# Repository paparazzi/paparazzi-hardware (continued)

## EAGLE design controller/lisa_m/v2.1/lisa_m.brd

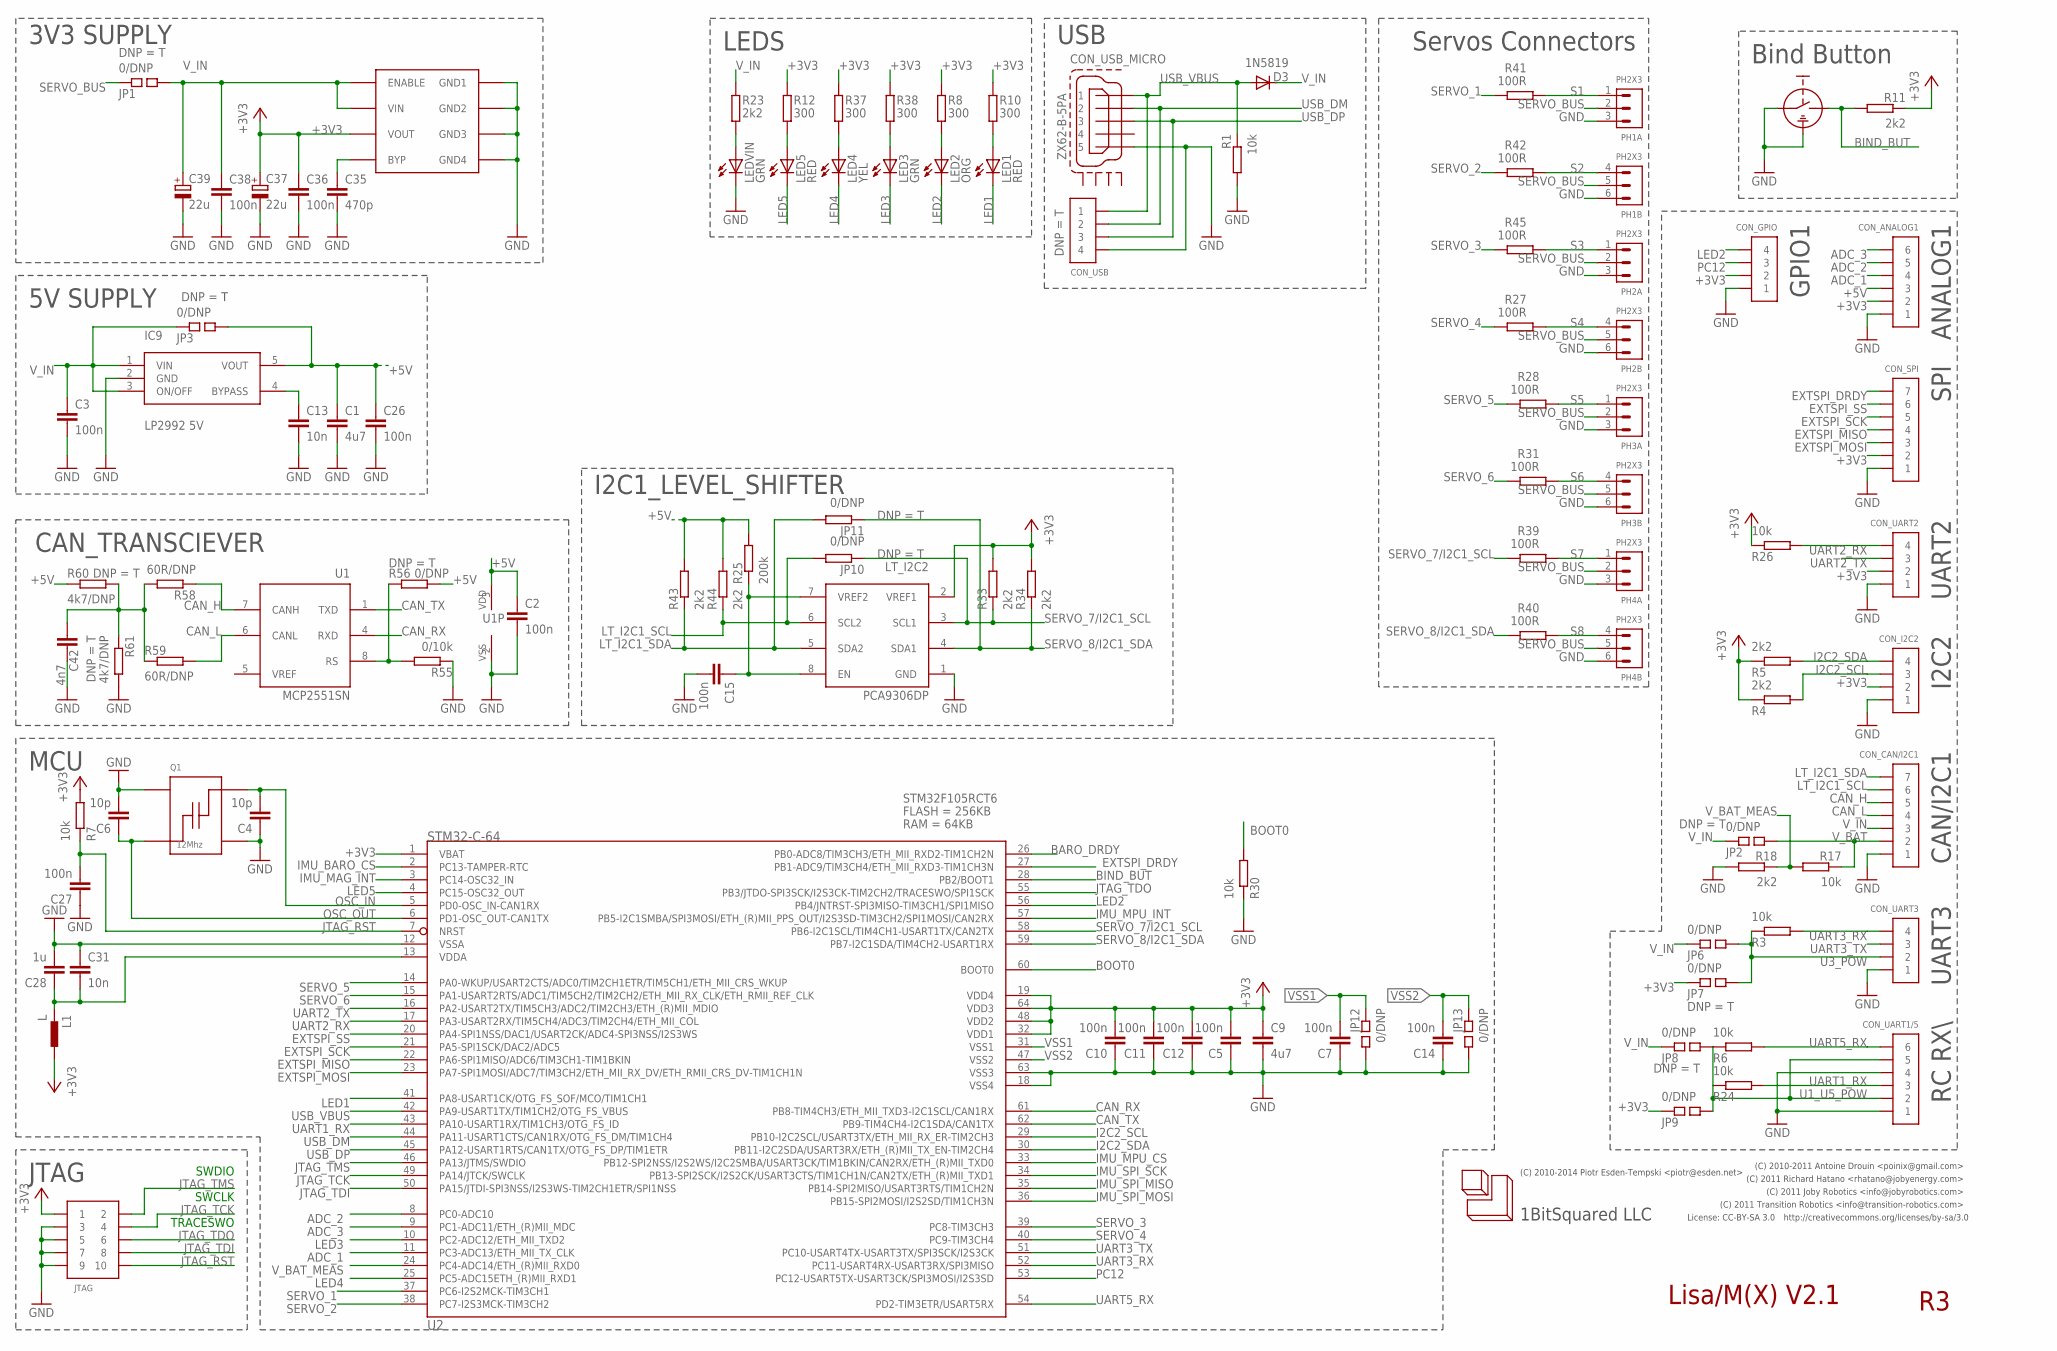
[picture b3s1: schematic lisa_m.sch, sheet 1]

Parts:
C1, C9: 4u7; 0603-CAP; PARTNO cap-cer-0603-4u7
C2, C3, C5, C7, C10, C11, C12, C14, C15, C26, C27, C36, C38: 100n; 0402-CAP; PARTNO cap-cer-0402-100n
C4, C6: 10p; 0402-CAP; PARTNO cap-cer-0402-10p
C13, C31: 10n; 0402-CAP; PARTNO cap-cer-0402-10n
C28: 1u; 0603-CAP; PARTNO cap-cer-0603-1u
C35: 470p; 0402-CAP; PARTNO cap-cer-0402-470p
C37, C39: 22u; 3528/B; PARTNO cap-tan-B-22u-16v
C42: 4n7; 0603-CAP; PARTNO cap-cer-0603-4n7
CON_ANALOG1: CONN_6-1-53398; PB-53398-06; PARTNO conn-picoblade-smd-0.05in-6-vert
CON_CAN/I2C1: CONN_7-1-53398; PB-53398-07; PARTNO conn-picoblade-smd-0.05in-7-vert
CON_GPIO: CONN_4-1-53398; PB-53398-04; PARTNO conn-picoblade-smd-0.05in-4-vert
CON_I2C2: CONN_4-1-53398; PB-53398-04; PARTNO conn-picoblade-smd-0.05in-4-vert
CON_SPI: CONN_7-1-53398; PB-53398-07; PARTNO conn-picoblade-smd-0.05in-7-vert
CON_UART1/5: CONN_6-1PB-53398-06_SMALL; PB-53398-06; PARTNO conn-picoblade-smd-0.05in-6-vert
CON_UART2, CON_UART3: CONN_4-1-53398; PB-53398-04; PARTNO conn-picoblade-smd-0.05in-4-vert
CON_USB: CONN_4-1-53047; PB-53047-04; PARTNO conn-picoblade-th-0.05in-4-vert
CON_USB_MICRO: ZX62-B-5PA; PARTNO conn-smd-usb-micro-b
D3: 1N5819; 0603-DIO; PARTNO diode-schottky-0603
IC9: LP2992 5V; SOT23-5; PARTNO vreg-sot-23-5-5v
JP1, JP2, JP3, JP6, JP7, JP8, JP9, JP12, JP13: 0/DNP; 0402-SQJMP; PARTNO res-0402-0
JP10, JP11: 0/DNP; 0603-RES; PARTNO res-0603-0
JTAG: PIN_HDR_EDG_1.27MM_5-2; FTSH-105-DV; PARTNO conn-smd-0.05in-5-2
L1: L; 0402-IND; PARTNO ferrite-0402-600
LED1: RED; 0402-LED; PARTNO led-0402-red
LED2: ORG; 0402-LED; PARTNO led-0402-org
LED3: GRN; 0402-LED; PARTNO led-0402-grn
LED4: YEL; 0402-LED; PARTNO led-0402-yel
LED5: RED; 0402-LED; PARTNO led-0402-grn
LEDVIN: GRN; 0402-LED; PARTNO led-0402-grn
LT_I2C2: PCA9306DP; TSSOP_B3; PARTNO ic-tssop8-level-trans
PH1, PH2, PH3, PH4: PH2X3; PH010-2-3
Q1: 12Mhz; ABM8; PARTNO xtal-abm8-12mhz
R1, R3, R6, R7, R17, R24, R26, R30: 10k; 0402-RES; PARTNO res-0402-10k
R4, R5, R11, R18, R23, R33, R34, R43, R44: 2k2; 0402-RES; PARTNO res-0402-2k2
R8, R10, R12, R37, R38: 300; 0402-RES; PARTNO res-0402-300
R25: 200k; 0402-RES; PARTNO res-0402-200k
R27, R28, R31, R39, R40, R41, R42, R45: 100R; 0402-RES; PARTNO res-0402-100
R55: 0/10k; 0402-RES; PARTNO res-0402-10k
R56: 0/DNP; 0402-RES; PARTNO res-0402-0
R58, R59: 60R/DNP; 0402-RES; PARTNO res-0402-60.4
R60, R61: 4k7/DNP; 0402-RES; PARTNO res-0402-4k7
SW1: MICROTACT_GND; PARTNO sw-tact-top-gnd-3.0-2.5
U1: MCP2551SN; SO-08; PARTNO ic-so8-can
U2: STM32-C-64; LQFP64; PARTNO ic-mcu-stm32f415rgt6
VREG1: MIC5209; SOIC8; PARTNO vreg-so8-3v3

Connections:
+3V3: C5.P$2 (2), C9.P$1 (1), C10.P$2 (2), C11.P$2 (2), C12.P$2 (2), C36.P$1 (1), C37.+, CON_ANALOG1.2, CON_GPIO.2, CON_I2C2.2, CON_SPI.2, CON_UART2.2, JP7.P$1 (1), JP9.P$1 (1), JTAG.1, L1.P$1 (1), LT_I2C2.2 (VREF1), R4.P$1 (1), R5.P$1 (1), R7.P$2 (2), R8.P$2 (2), R10.P$2 (2), R11.P$1 (1), R12.P$2 (2), R26.P$1 (1), R33.P$2 (2), R34.P$2 (2), R37.P$2 (2), R38.P$2 (2), U2.1 (VBAT), U2.19 (VDD4), U2.32 (VDD1), U2.48 (VDD2), U2.64 (VDD3), VREG1.3 (VOUT); also elsewhere on the board
+5V: C1.P$1 (1), C2.P$1 (1), C26.P$1 (1), CON_ANALOG1.3, IC9.5 (VOUT), JP3.P$2 (2), R25.P$2 (2), R43.P$2 (2), R44.P$2 (2), R56.P$2 (2), R60.P$1 (1), U1.3 (VDD)
ADC_1: CON_ANALOG1.4, U2.11 (PC3-ADC13/ETH_MII_TX_CLK)
ADC_2: CON_ANALOG1.5, U2.8 (PC0-ADC10)
ADC_3: CON_ANALOG1.6, U2.9 (PC1-ADC11/ETH_(R)MII_MDC)
BARO_DRDY: U2.26 (PB0-ADC8/TIM3CH3/ETH_MII_RXD2-TIM1CH2N)
BIND_BUT: R11.P$2 (2), SW1.2, U2.28 (PB2/BOOT1)
BOOT0: R30.P$2 (2), U2.60 (BOOT0)
CAN_CENTER: C42.P$2 (2), R58.P$2 (2), R59.P$1 (1), R60.P$2 (2), R61.P$1 (1)
CAN_H: CON_CAN/I2C1.5, R58.P$1 (1), U1.7 (CANH)
CAN_L: CON_CAN/I2C1.4, R59.P$2 (2), U1.6 (CANL)
CAN_RX: U1.4 (RXD), U2.61 (PB8-TIM4CH3/ETH_MII_TXD3-I2C1SCL/CAN1RX)
CAN_TX: U1.1 (TXD), U2.62 (PB9-TIM4CH4-I2C1SDA/CAN1TX)
EXTSPI_DRDY: CON_SPI.7, U2.27 (PB1-ADC9/TIM3CH4/ETH_MII_RXD3-TIM1CH3N)
EXTSPI_MISO: CON_SPI.4, U2.22 (PA6-SPI1MISO/ADC6/TIM3CH1-TIM1BKIN)
EXTSPI_MOSI: CON_SPI.3, U2.23 (PA7-SPI1MOSI/ADC7/TIM3CH2/ETH_MII_RX_DV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)
EXTSPI_SCK: CON_SPI.5, U2.21 (PA5-SPI1SCK/DAC2/ADC5)
EXTSPI_SS: CON_SPI.6, U2.20 (PA4-SPI1NSS/DAC1/USART2CK/ADC4-SPI3NSS/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)
GND: C1.P$2 (2), C2.P$2 (2), C3.P$2 (2), C4.P$1 (1), C5.P$1 (1), C6.P$2 (2), C7.P$1 (1), C9.P$2 (2), C10.P$1 (1), C11.P$1 (1), C12.P$1 (1), C13.P$2 (2), C14.P$1 (1), C15.P$2 (2), C26.P$2 (2), C27.P$1 (1), C28.P$2 (2), C31.P$1 (1), C35.P$2 (2), C36.P$2 (2), C37.-, C38.P$2 (2), C39.-, C42.P$1 (1), CON_ANALOG1.1, CON_CAN/I2C1.1, CON_GPIO.1, CON_I2C2.1, CON_SPI.1, CON_UART1/5.1, CON_UART1/5.4, CON_UART2.1, CON_UART3.1, CON_USB.4, CON_USB_MICRO.PIN_5 (5), IC9.2 (GND), JP12.P$2 (2), JP13.P$2 (2), JTAG.3, JTAG.5, JTAG.7, JTAG.9, LEDVIN.C, LT_I2C2.1 (GND), PH1.3, PH1.6 (3), PH2.3, PH2.6 (3), PH3.3, PH3.6 (3), PH4.3, PH4.6 (3), Q1.P$2, Q1.P$4, R1.P$2 (2), R18.P$2 (2), R30.P$1 (1), R55.P$1 (1), R61.P$2 (2), SW1.1, SW1.G (GND), U1.2 (VSS), U2.12 (VSSA), U2.18 (VSS4), U2.63 (VSS3), VREG1.5 (GND4), VREG1.6 (GND3), VREG1.7 (GND2), VREG1.8 (GND1); also elsewhere on the board
I2C2_SCL: CON_I2C2.3, R4.P$2 (2), U2.29 (PB10-I2C2SCL/USART3TX/ETH_MII_RX_ER-TIM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)
I2C2_SDA: CON_I2C2.4, R5.P$2 (2), U2.30 (PB11-I2C2SDA/USART3RX/ETH_(R)MII_TX_EN-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)
IMU_BARO_CS: U2.2 (PC13-TAMPER-RTC); also elsewhere on the board
IMU_MAG_INT: U2.3 (PC14-OSC32_IN); also elsewhere on the board
IMU_MPU_CS: U2.33 (PB12-SPI2NSS/I2S2WS/I2C2SMBA/USART3CK/T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); also elsewhere on the board
IMU_MPU_INT: U2.57 (PB5-I2C1SMBA/SPI3MOSI/ETH_(R)MII_PPS_OU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); also elsewhere on the board
IMU_SPI_MISO: U2.35 (PB14-SPI2MISO/USART3RTS/TIM1CH2N); also elsewhere on the board
IMU_SPI_MOSI: U2.36 (PB15-SPI2MOSI/I2S2SD/TIM1CH3N); also elsewhere on the board
IMU_SPI_SCK: U2.34 (PB13-SPI2SCK/I2S2CK/USART3CTS/TIM1CH1N/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); also elsewhere on the board
JTAG_RST: C27.P$2 (2), JTAG.10, R7.P$1 (1), U2.7 (NRST)
JTAG_TCK: JTAG.4, U2.49 (PA14/JTCK/SWCLK)
JTAG_TDI: JTAG.8, U2.50 (PA15/JTDI-SPI3NSS/I2S3WS-TIM2CH1ETR/SPI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)
JTAG_TDO: JTAG.6, U2.55 (PB3/JTDO-SPI3SCK/I2S3CK-TIM2CH2/TRACESW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)
JTAG_TMS: JTAG.2, U2.46 (PA13/JTMS/SWDIO)
LED1: LED1.C, U2.41 (PA8-USART1CK/OTG_FS_SOF/MCO/TIM1CH1)
LED2: CON_GPIO.4, LED2.C, U2.56 (PB4/JNTRST-SPI3MISO-TIM3CH1/SPI1MISO)
LED3: LED3.C, U2.10 (PC2-ADC12/ETH_MII_TXD2)
LED4: LED4.C, U2.25 (PC5-ADC15ETH_(R)MII_RXD1)
LED5: LED5.C, U2.4 (PC15-OSC32_OUT)
LT_I2C1_SCL: CON_CAN/I2C1.6, JP10.P$2 (2), LT_I2C2.6 (SCL2), R44.P$1 (1)
LT_I2C1_SDA: CON_CAN/I2C1.7, JP11.P$2 (2), LT_I2C2.5 (SDA2), R43.P$1 (1)
unnamed: R55.P$2 (2), R56.P$1 (1), U1.8 (RS)
unnamed: LED1.A, R10.P$1 (1)
unnamed: C13.P$1 (1), IC9.4 (BYPASS)
unnamed: C35.P$1 (1), VREG1.4 (BYP)
unnamed: C15.P$1 (1), LT_I2C2.7 (VREF2), LT_I2C2.8 (EN), R25.P$1 (1)
unnamed: LED2.A, R8.P$1 (1)
unnamed: LEDVIN.A, R23.P$1 (1)
unnamed: LED5.A, R12.P$1 (1)
unnamed: LED4.A, R37.P$1 (1)
unnamed: LED3.A, R38.P$1 (1)
OSC_IN: C4.P$2 (2), Q1.P$3, U2.5 (PD0-OSC_IN-CAN1RX)
OSC_OUT: C6.P$1 (1), Q1.P$1, U2.6 (PD1-OSC_OUT-CAN1TX)
PC12: CON_GPIO.3, U2.53 (PC12-USART5TX-USART3CK/SPI3MOSI/I2S3SD)
S1: PH1.1, R41.P$1 (1)
S2: PH1.4 (1), R42.P$1 (1)
S3: PH2.1, R45.P$1 (1)
S4: PH2.4 (1), R27.P$1 (1)
S5: PH3.1, R28.P$1 (1)
S6: PH3.4 (1), R31.P$1 (1)
S7: PH4.1, R39.P$1 (1)
S8: PH4.4 (1), R40.P$1 (1)
SERVO_1: R41.P$2 (2), U2.37 (PC6-I2S2MCK-TIM3CH1)
SERVO_2: R42.P$2 (2), U2.38 (PC7-I2S3MCK-TIM3CH2)
SERVO_3: R45.P$2 (2), U2.39 (PC8-TIM3CH3)
SERVO_4: R27.P$2 (2), U2.40 (PC9-TIM3CH4)
SERVO_5: R28.P$2 (2), U2.14 (PA0-WKUP/USART2CTS/ADC0/TIM2CH1ETR/TIM5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)
SERVO_6: R31.P$2 (2), U2.15 (PA1-USART2RTS/ADC1/TIM5CH2/TIM2CH2/ETH_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)
SERVO_7/I2C1_SCL: JP10.P$1 (1), LT_I2C2.3 (SCL1), R33.P$1 (1), R39.P$2 (2), U2.58 (PB6-I2C1SCL/TIM4CH1-USART1TX/CAN2TX)
SERVO_8/I2C1_SDA: JP11.P$1 (1), LT_I2C2.4 (SDA1), R34.P$1 (1), R40.P$2 (2), U2.59 (PB7-I2C1SDA/TIM4CH2-USART1RX)
SERVO_BUS: JP1.P$1 (1), PH1.2, PH1.5 (2), PH2.2, PH2.5 (2), PH3.2, PH3.5 (2), PH4.2, PH4.5 (2)
U1_U5_POW: CON_UART1/5.2, CON_UART1/5.5, JP8.P$2 (2), JP9.P$2 (2), R6.P$1 (1), R24.P$1 (1)
U3_POW: CON_UART3.2, JP6.P$2 (2), JP7.P$2 (2), R3.P$1 (1)
UART1_RX: CON_UART1/5.3, R24.P$2 (2), U2.43 (PA10-USART1RX/TIM1CH3/OTG_FS_ID)
UART2_RX: CON_UART2.4, R26.P$2 (2), U2.17 (PA3-USART2RX/TIM5CH4/ADC3/TIM2CH4/ETH_M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)
UART2_TX: CON_UART2.3, U2.16 (PA2-USART2TX/TIM5CH3/ADC2/TIM2CH3/ETH_(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)
UART3_RX: CON_UART3.4, R3.P$2 (2), U2.52 (PC11-USART4RX-USART3RX/SPI3MISO)
UART3_TX: CON_UART3.3, U2.51 (PC10-USART4TX-USART3TX/SPI3SCK/I2S3CK)
UART5_RX: CON_UART1/5.6, R6.P$2 (2), U2.54 (PD2-TIM3ETR/USART5RX)
USB_DM: CON_USB.2, CON_USB_MICRO.PIN_2 (2), U2.44 (PA11-USART1CTS/CAN1RX/OTG_FS_DM/TIM1CH4)
USB_DP: CON_USB.3, CON_USB_MICRO.PIN_3 (3), U2.45 (PA12-USART1RTS/CAN1TX/OTG_FS_DP/TIM1ETR)
USB_VBUS: CON_USB.1, CON_USB_MICRO.PIN_1 (1), D3.A, R1.P$1 (1), U2.42 (PA9-USART1TX/TIM1CH2/OTG_FS_VBUS)
VDDA: C28.P$1 (1), C31.P$2 (2), L1.P$2 (2), U2.13 (VDDA)
VREF: U1.5 (VREF)
VSS1: C7.P$2 (2), JP12.P$1 (1), U2.31 (VSS1)
VSS2: C14.P$2 (2), JP13.P$1 (1), U2.47 (VSS2)
V_BAT: CON_CAN/I2C1.2, JP2.P$2 (2), R17.P$1 (1)
V_BAT_MEAS: R17.P$2 (2), R18.P$1 (1), U2.24 (PC4-ADC14/ETH_(R)MII_RXD0)
V_IN: C3.P$1 (1), C38.P$1 (1), C39.+, CON_CAN/I2C1.3, D3.C, IC9.1 (VIN), IC9.3 (ON/OFF), JP1.P$2 (2), JP2.P$1 (1), JP3.P$1 (1), JP6.P$1 (1), JP8.P$1 (1), R23.P$2 (2), VREG1.1 (ENABLE), VREG1.2 (VIN); also elsewhere on the board

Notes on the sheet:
Servos Connectors
3V3 SUPPLY
5V SUPPLY
License: CC-BY-SA 3.0
http://creativecommons.org/licenses/by-sa/3.0
(C) 2010-2014 Piotr Esden-Tempski <piotr@esden.net>
(C) 2010-2011 Antoine Drouin <poinix@gmail.com>
(C) 2011 Richard Hatano <rhatano@jobyenergy.com>
(C) 2011 Joby Robotics <info@jobyrobotics.com>
(C) 2011 Transition Robotics <info@transition-robotics.com>
Bind Button
1BitSquared LLC
JTAG
SWDIO
SWCLK
TRACESWO
MCU
LEDS
USB
SPI
I2C2
ANALOG1
GPIO1
UART3
UART2
RC RX\
CAN/I2C1
I2C1_LEVEL_SHIFTER
CAN_TRANSCIEVER
Lisa/M(X) V2.1

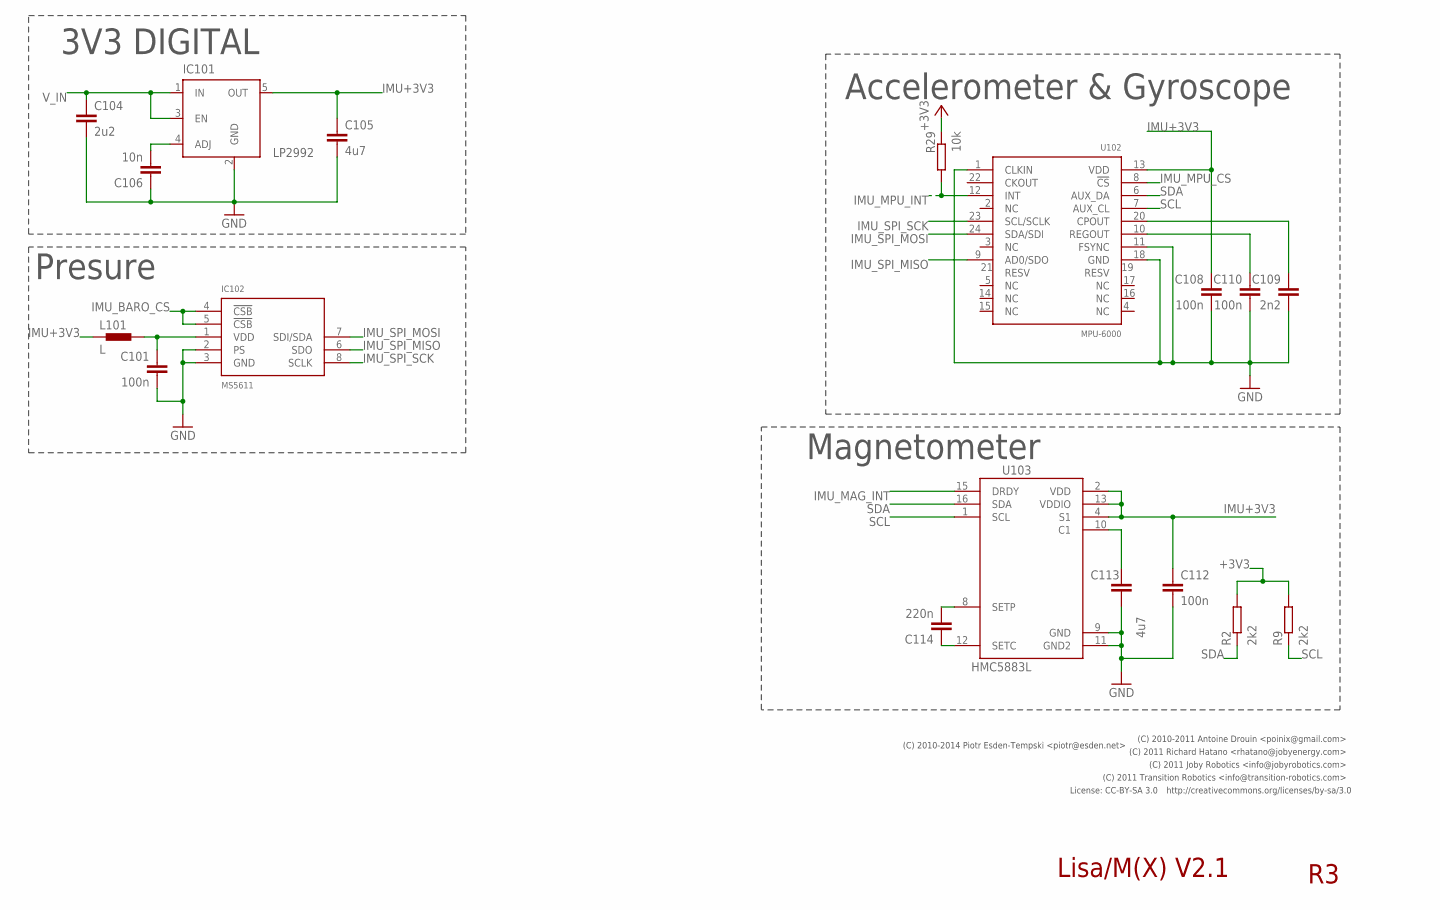
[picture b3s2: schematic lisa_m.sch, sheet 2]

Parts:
C101, C108, C110, C112: 100n; 0402-CAP; PARTNO cap-cer-0402-100n
C104: 2u2; 0603-CAP; PARTNO cap-cer-0603-2u2
C105, C113: 4u7; 0603-CAP; PARTNO cap-cer-0603-4u7
C106: 10n; 0402-CAP; PARTNO cap-cer-0402-10n
C109: 2n2; 0402-CAP; PARTNO cap-cer-0402-2n2
C114: 220n; 0603-CAP; PARTNO cap-cer-0603-220n
IC101: LP2992; SOT23-5; PARTNO vreg-sot23-5-3v3
IC102: MS5611; QFN-MS5611; PARTNO ic-sensr-ms5611
L101: L; 0402-IND; PARTNO ferrite-0402-600
R2, R9: 2k2; 0402-RES; PARTNO res-0402-2k2
R29: 10k; 0402-RES; PARTNO res-0402-10k
U102: MPU-6000; QFN24-NO-PAD; PARTNO ic-sensr-mpu6000
U103: HMC5883L; LPCC16-HMC5883L; PARTNO ic-sensr-hmc5883l

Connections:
+3V3: R2.P$2 (2), R9.P$2 (2), R29.P$1 (1); also elsewhere on the board
BARO_+3V3: C101.P$1 (1), IC102.1 (VDD), L101.P$1 (1)
GND: C101.P$2 (2), C104.P$2 (2), C105.P$2 (2), C106.P$1 (1), C108.P$2 (2), C109.P$2 (2), C110.P$2 (2), C112.P$2 (2), C113.P$2 (2), IC101.2 (GND), IC102.2 (PS), IC102.3 (GND), U102.1 (CLKIN), U102.11 (FSYNC), U102.18 (GND), U103.9 (GND), U103.11 (GND2); also elsewhere on the board
IMU+3V3: C105.P$1 (1), C108.P$1 (1), C112.P$1 (1), IC101.5 (OUT), L101.P$2 (2), U102.13 (VDD), U103.2 (VDD), U103.4 (S1), U103.13 (VDDIO)
IMU_BARO_CS: IC102.4 (!CSB), IC102.5 (!CSB); also elsewhere on the board
IMU_MAG_INT: U103.15 (DRDY); also elsewhere on the board
IMU_MPU_CS: U102.8 (!CS); also elsewhere on the board
IMU_MPU_INT: R29.P$2 (2), U102.12 (INT); also elsewhere on the board
IMU_SPI_MISO: IC102.6 (SDO), U102.9 (AD0/SDO); also elsewhere on the board
IMU_SPI_MOSI: IC102.7 (SDI/SDA), U102.24 (SDA/SDI); also elsewhere on the board
IMU_SPI_SCK: IC102.8 (SCLK), U102.23 (SCL/SCLK); also elsewhere on the board
unnamed: C109.P$1 (1), U102.20 (CPOUT)
unnamed: C110.P$1 (1), U102.10 (REGOUT)
unnamed: C113.P$1 (1), U103.10 (C1)
unnamed: C106.P$2 (2), IC101.4 (ADJ)
unnamed: C114.P$2 (2), U103.8 (SETP)
unnamed: C114.P$1 (1), U103.12 (SETC)
SCL: R9.P$1 (1), U102.7 (AUX_CL), U103.1 (SCL)
SDA: R2.P$1 (1), U102.6 (AUX_DA), U103.16 (SDA)
V_IN: C104.P$1 (1), IC101.1 (IN), IC101.3 (EN); also elsewhere on the board

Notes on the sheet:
3V3 DIGITAL
Magnetometer
Accelerometer & Gyroscope
Presure
License: CC-BY-SA 3.0
http://creativecommons.org/licenses/by-sa/3.0
(C) 2010-2014 Piotr Esden-Tempski <piotr@esden.net>
(C) 2011 Richard Hatano <rhatano@jobyenergy.com>
(C) 2011 Joby Robotics <info@jobyrobotics.com>
(C) 2011 Transition Robotics <info@transition-robotics.com>
(C) 2010-2011 Antoine Drouin <poinix@gmail.com>
Lisa/M(X) V2.1

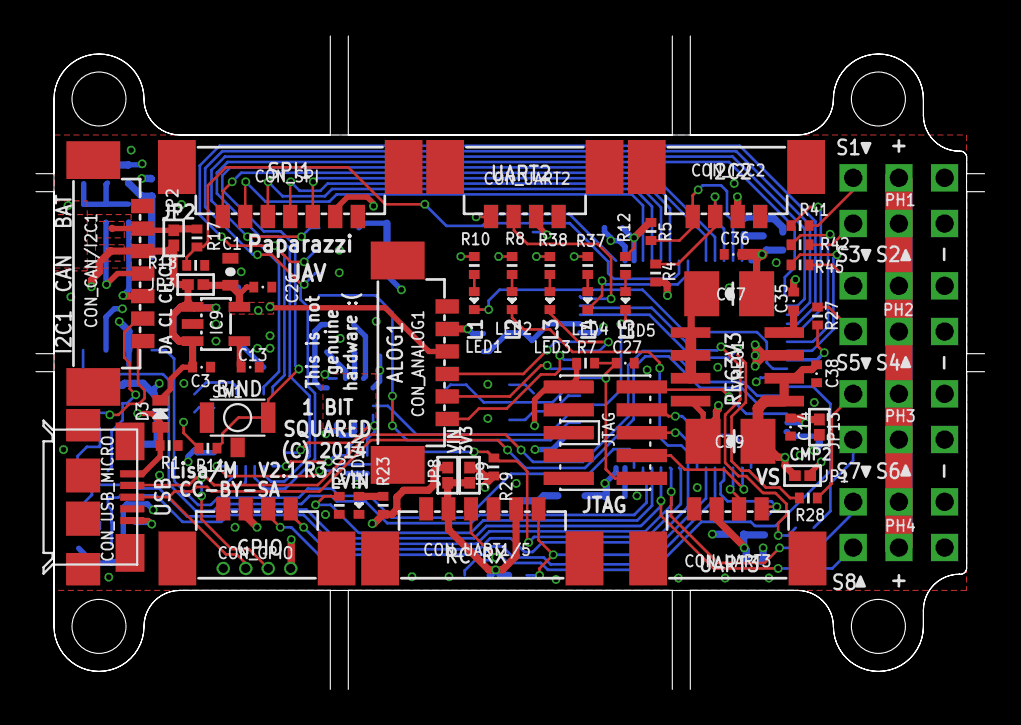
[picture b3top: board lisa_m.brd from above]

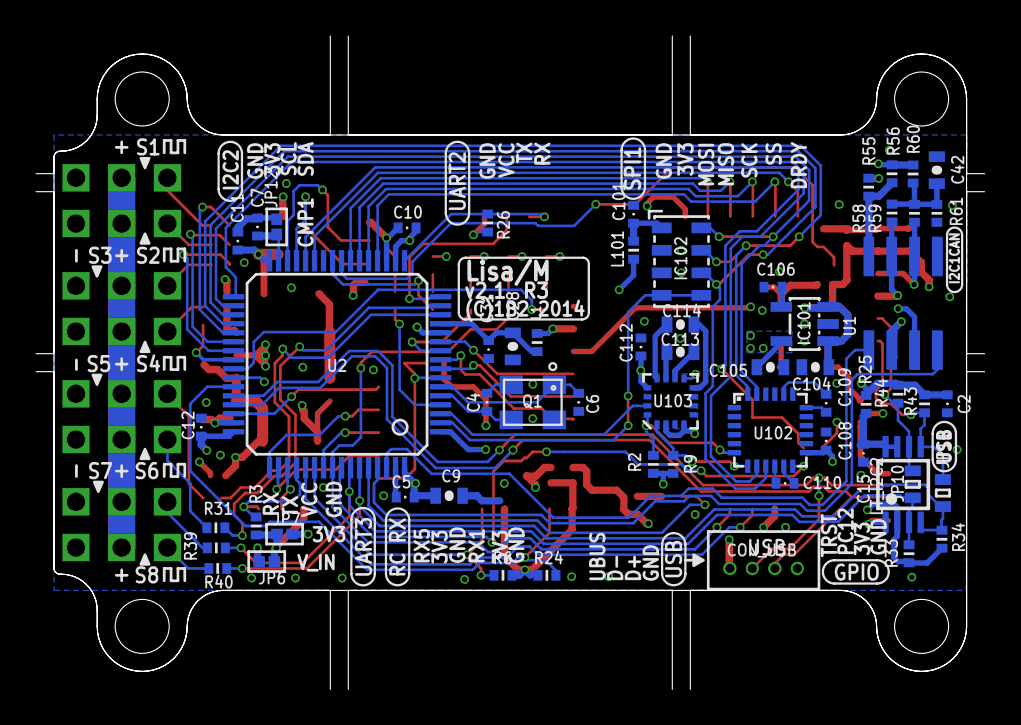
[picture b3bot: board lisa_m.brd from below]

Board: 4 copper layers, 52.7 x 36.3 mm, 120 parts (59 on the bottom side), 96 nets.

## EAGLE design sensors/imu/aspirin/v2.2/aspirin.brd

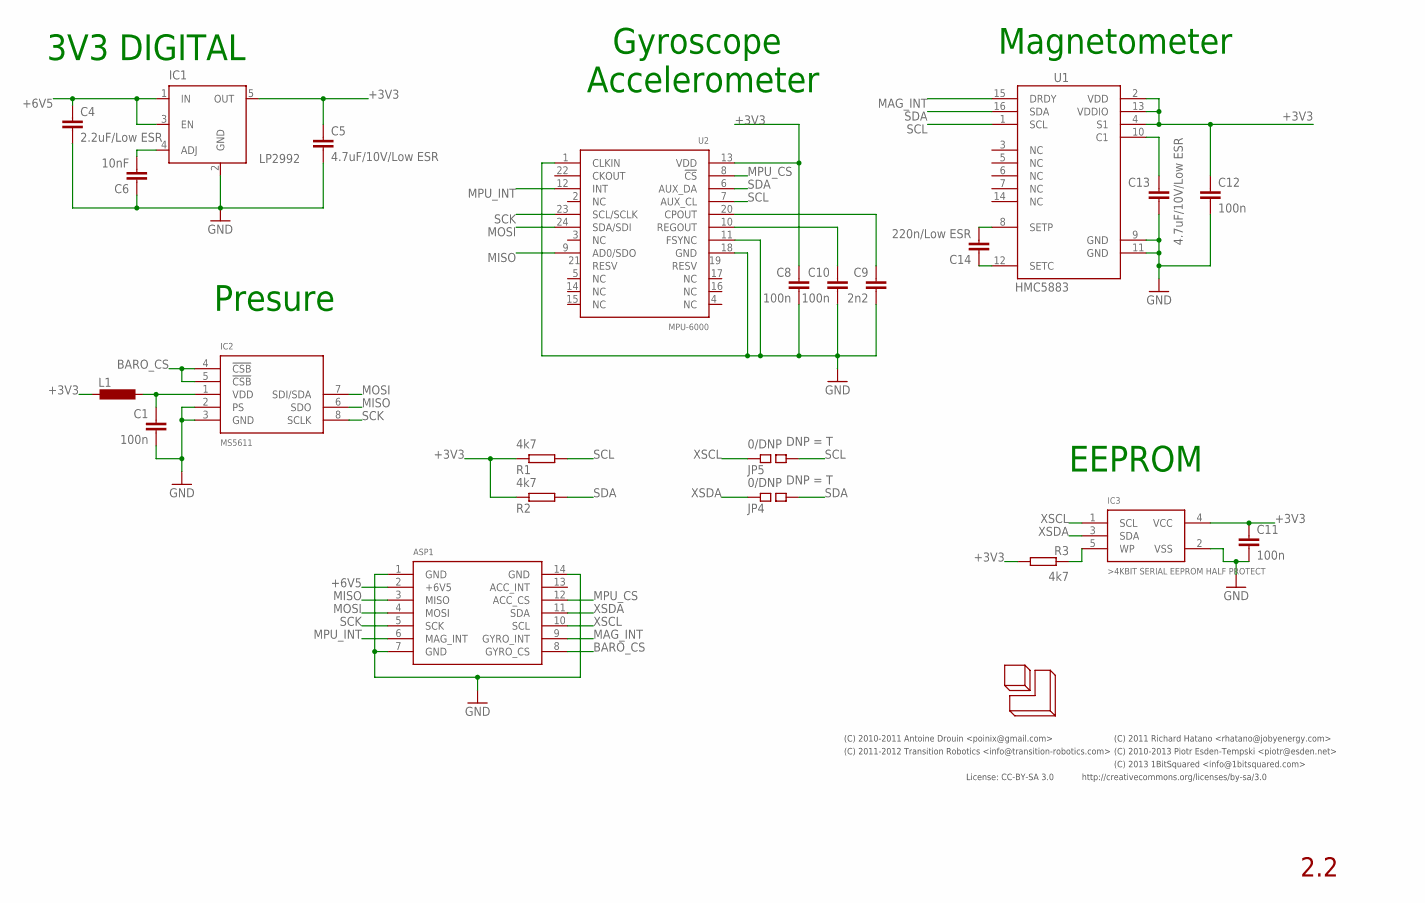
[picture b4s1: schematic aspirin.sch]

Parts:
ASP1: ASPIRIN; ASPIRIN_CASTELLATED; PARTNO pcb-aspirin
C1, C8, C10, C11, C12: 100n; 0402-CAP; PARTNO cap-cer-0402-100n
C4: 2.2uF/Low ESR; 0603-CAP; PARTNO cap-cer-0603-2u2
C5, C13: 4.7uF/10V/Low ESR; 0603-CAP; PARTNO cap-cer-0603-4u7
C6: 10nF; 0402-CAP; PARTNO cap-cer-0402-10n
C9: 2n2; 0402-CAP; PARTNO cap-cer-0402-2n2
C14: 220n/Low ESR; 0603-CAP; PARTNO cap-cer-0603-220n
IC1: LP2992; SOT23-5; PARTNO vreg-sot-23-5-3v3
IC2: MS5611; QFN-MS5611; PARTNO sensr-qfn-8-baro
IC3: >4KBIT SERIAL EEPROM HALF PROTECT; SOT23-5; PARTNO ic-sot-23-5-4k-eeprom
JP4, JP5: 0/DNP; 0402-SQJMP; PARTNO res-0402-0
L1: INDUCTOR-0603; 0603-IND; PARTNO ferrite-0603-600ohm
R1, R2, R3: 4k7; 0402-RES; PARTNO res-0402-4k7
U1: HMC5883; PLCC16-HMC5883; PARTNO sensr-plcc-16-mag
U2: MPU-6000; QFN24-NO-PAD; PARTNO sensr-qfn-24-acc-gyro
U$2: 1B2-NEW-LOGO-3MM

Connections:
+3V3: C5.P$1 (1), C8.P$1 (1), C11.P$1 (1), C12.P$1 (1), IC1.5 (OUT), IC3.4 (VCC), L1.P$2 (2), R1.P$1 (1), R2.P$1 (1), R3.P$2 (2), U1.2 (VDD), U1.4 (S1), U1.13 (VDDIO), U2.13 (VDD)
+6V5: ASP1.2 (+6V5), C4.P$1 (1), IC1.1 (IN), IC1.3 (EN)
BARO_+3V3: C1.P$1 (1), IC2.1 (VDD), L1.P$1 (1)
BARO_CS: ASP1.8 (GYRO_CS), IC2.4 (!CSB), IC2.5 (!CSB)
GND: ASP1.1 (GND), ASP1.7 (GND), ASP1.14 (GND), C1.P$2 (2), C4.P$2 (2), C5.P$2 (2), C6.P$1 (1), C8.P$2 (2), C9.P$2 (2), C10.P$2 (2), C11.P$2 (2), C12.P$2 (2), C13.P$2 (2), IC1.2 (GND), IC2.2 (PS), IC2.3 (GND), IC3.2 (VSS), U1.9 (GND), U1.11 (GND), U2.1 (CLKIN), U2.11 (FSYNC), U2.18 (GND)
MAG_INT: ASP1.9 (GYRO_INT), U1.15 (DRDY)
MISO: ASP1.3 (MISO), IC2.6 (SDO), U2.9 (AD0/SDO)
MOSI: ASP1.4 (MOSI), IC2.7 (SDI/SDA), U2.24 (SDA/SDI)
MPU_CS: ASP1.12 (ACC_CS), U2.8 (!CS)
MPU_INT: ASP1.6 (MAG_INT), U2.12 (INT)
unnamed: C9.P$1 (1), U2.20 (CPOUT)
unnamed: C10.P$1 (1), U2.10 (REGOUT)
unnamed: C13.P$1 (1), U1.10 (C1)
unnamed: IC3.5 (WP), R3.P$1 (1)
unnamed: C6.P$2 (2), IC1.4 (ADJ)
unnamed: C14.P$2 (2), U1.8 (SETP)
unnamed: C14.P$1 (1), U1.12 (SETC)
SCK: ASP1.5 (SCK), IC2.8 (SCLK), U2.23 (SCL/SCLK)
SCL: JP5.P$2 (2), R1.P$2 (2), U1.1 (SCL), U2.7 (AUX_CL)
SDA: JP4.P$2 (2), R2.P$2 (2), U1.16 (SDA), U2.6 (AUX_DA)
XSCL: ASP1.10 (SCL), IC3.1 (SCL), JP5.P$1 (1)
XSDA: ASP1.11 (SDA), IC3.3 (SDA), JP4.P$1 (1)

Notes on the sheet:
3V3 DIGITAL
Gyroscope
EEPROM
Magnetometer
Accelerometer
2.2
Presure
License: CC-BY-SA 3.0
http://creativecommons.org/licenses/by-sa/3.0
(C) 2010-2013 Piotr Esden-Tempski <piotr@esden.net>
(C) 2010-2011 Antoine Drouin <poinix@gmail.com>
(C) 2011 Richard Hatano <rhatano@jobyenergy.com>
(C) 2011-2012 Transition Robotics <info@transition-robotics.com>
(C) 2013 1BitSquared <info@1bitsquared.com>

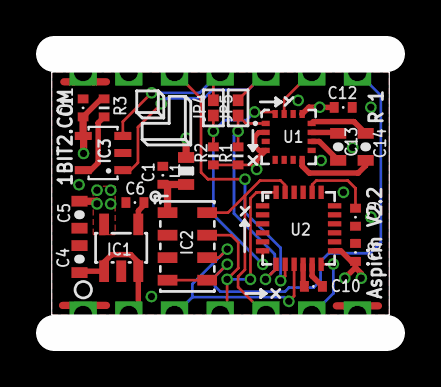
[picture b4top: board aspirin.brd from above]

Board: 4 copper layers, 18.5 x 15.5 mm, 24 parts (0 on the bottom side), 22 nets.

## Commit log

2011-11-24 Initial commit after a coarce cleanup. For older revisions check the hardware svn repository on Savannah. http://svn.savannah.nongnu.org/viewvc/paparazzi-hardware/trunk/?root=paparazzi
2011-11-24 Reorganized sensor directory a bit.
2011-12-01 Starting work on lia v1.0 controller board.
    It is based on lisa/m and uses throughole 0.1" pin headers instead of
    molex picoblade.
2011-12-01 Added BEC balance inline resistors.
2011-12-02 Improved silkscreen.
2011-12-05 Added castellated hole aspirin footprint.
2011-12-05 Starting revised aspirn v2.1. Added i2c jumpers.
2011-12-05 Added MS5611 to the library.
2011-12-05 Corrected polarity on MS5611 CS pins.
2011-12-05 Added MS5611 to the schematic.
2011-12-05 Removed restrict on MS5611 footprint.
2011-12-05 Added MS5611 to the layout and routed.
2011-12-05 Added pull-ups to local i2c and it is probably a good idea to supply the pressure sensor with power...
    * The i2c pullups are not quoted in any of the mpu-6000 datasheets
    explicitely there is a very unlikely chance that they may not needed.
    Needs to be tested.
    * Connected VDD to +3v3 (seriously no comment ...)
2012-01-12 Updated the population attributes for lia.
2012-01-13 Started Lisa/M V2.1. Swapped the labeling of Analog1 and Analog2 connectors to be more sensible and adhering to the documentation in the wiki. fixes #5
2012-01-13 Swapped labeling of Analog1 and Analog2 connectors to make the naming more sensible.
2012-01-13 Connected the pressure sensor to the MPU-6000. fixes #1
    Now using the auxilary I2C interface instead of the host MCU SPI.
    This will allow reading out of almost all sensor data in one time
    syncronous spi data burst from the MPU-6000.
2012-01-13 Corrected the coordinate system symbol on the silkscreen. fixes #2
2012-01-13 Added DNP attributes to jumpers.
2012-01-13 Increased size of the magnetometer caps to improve performance. fixes #4
    The new size of the HMC magnetometer caps is 0603 otherwise it is
    difficult to get low esr versions of those to gain good performance.
2012-01-16 Some layer cleanup.
2012-01-16 Moved board to origin.
2012-01-16 Added panel rails for lia.
2012-01-17 Approved two remaining drc warnings.
2012-01-17 Generated teardropped version of lia.
2012-01-17 Removed three unnecessary solderstop windows. Fixed solderstop layer comments.
2012-01-17 Added gerber generation files for lia.
2012-01-18 Increased annular rings on lia to 5mil.
2012-01-18 Some more tweaks for DRC satisfaction. Regenerated teardrops.
2012-01-18 Some modifications to satisfy DRC and generated teardropped version.
2012-01-19 Added panel generation to aspirin 2.1.
2012-01-19 Some more DRC improvements.
2012-01-20 Updated bom-ex id designators to be more readable, unique and consistent.
2012-01-20 Updated bom-ex id's to be more consistent, readable and unique.
2012-01-20 Some last minute DRC changes for prototype production run.
2012-01-21 Updated bom-x designators for parts.
2012-01-21 Replaced some blue led's with amber and green ones.
2012-01-23 Changed the resistors for non blue leds to 300ohm.
2012-01-23 Made schematic and brd consistent again.
2012-01-27 More BOM tweaking, also readded the micro USB to lia.
2012-01-27 Minor tweaks to the placement plan.
2012-01-31 Added milling and scoring information.
2012-01-31 Moved vscore 5mil out for better clearence.
2012-01-31 Adjusted horizontal spacing to overlap vscores.
2012-02-01 Removed fiducials on the board, we have them on the rails.
2012-02-01 Added eeprom WP pullup.
2012-02-01 Updated licensing information.
2012-02-01 Updated teardropped aspirin and switched gerber generation to use that instead.
2012-02-01 Added panel rail.
2012-02-01 Added comment about castellated holes.
2012-02-04 Went back to 4layer design. Removed restrict's under the mag and mpu. Removed traces under the MPU based on datasheet recommendations.
2012-02-04 Adding alternative routing of aspirin 2.1. May be a bit cleaner? GYRO_INT and MAG_INT signals are swapped and magnetometer and MPU positions are swapped too.
2012-02-06 Added some more files to gitignore.
2012-02-06 Converted all eagle files to Eagle 6 format.
2012-02-06 Added booz imu v1.2 board files.
2012-02-06 Aspirin alt design is cleaner, made it the official routing of v2.1.
2012-02-06 Switched gerber generation back to non teardropped PCB. As well as changed the panel geometry.
2012-02-06 Reapproved DRC errors.
2012-02-07 Added smaller panel definitions for prototyping purposes.
2012-02-08 Added gtop gps schematic and board files.
2012-02-15 Moved and resized the coordinate system symbol on the silkscreen.
2012-02-15 Moved mag SDA via to connect both sides of the bottom 3V3 plane.
2012-02-16 Some minor cleanups and touchups. Renamed signal silkscreen legend's to better reflect reality.
2012-02-17 Renamed ACC_CS to MPU_CS and changed panel to 3x3.
2012-02-17 Changed via size to 0.4mm.
2012-02-22 Added ublox gps board files.
2012-03-05 Minor final fixes before going into assembly.
2012-03-13 Added SparkFun based xbee carrier with picoblade connector.
2012-03-13 Added gerber generation files for xbee carrier.
2012-03-13 Removed solder stop from vias on the xbee_carrier.
2012-04-03 Added autopilot Tiny v2.11
2012-04-03 Yapa2
2012-04-04 moved Tiny files from v2.1 for v2.11
2012-04-13 Paparazzi Logger (MM/CDW)
2012-05-07 - switched analog1 and analog2 connector labels on schematic and silkscreen - changed LED labels on schematic to be more intuitive and match software defines - changed power led to LEDVIN from LED4 (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
2012-05-07 changed LED labeling to be more intuitive for a user, both on schematic and on silkscreens, also changed power led schematic name to LEDVIN to keep better consistency with silkscreen and remove numbe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
2012-05-07 switched UART1 and UART3 silkscreen labels to be correct
2012-05-07 updated the uart1/3 labeling on silkscreen, unsmashed some LED labels
2012-05-07 Bumped the layer markings to R1.
2012-05-07 Initial commit of lia 1.1.
    Changes from 1.0 to now:
    * Replaced pin header with micro usb connector
    * Rotated top silkscreen labels 180 to show up readable in the quadshot
    airframe.
    * Repositioned the side pinheaders to fit into a breadboard.
    * Removed pressure sensor footprint.
2012-05-10 Added gerber generation scripts to lia v1.1.
2012-05-21 Fixed the corner pin intended for GYRO_CS to be disconnected from ground and labeled RESV on the pcb.
2012-05-21 Added booz imu v1.02
2012-05-23 Added bom-x attributes and connected the tantalum to ground.
2012-06-21 Added a proposal for an improved Aspirin V2.2.
2012-09-28 Added panelization files to aspirin v2.2.
2012-10-01 Minor touchups.
2012-12-04 add external 8x servo board
2013-02-25 Version controlled TWOG_v1.0
2013-03-01 Add I2C multi board
2013-03-02 Add 8x I2C multi connector
2013-03-02 Add Melexis MLX90614 infrared thermometer with I2C interface.
2013-03-02 Add Sensirion SHT75 adapter board for proprietary digital interface
2013-03-12 add SHT2x breakout board
2013-03-12 update SHT75
2013-03-17 small corrections, add pdf schematics: i2c_multi, sht75, mlx90614 and sht25
2013-03-17 add I2C multi adapter
2013-10-18 Updated gerber generation files.
2013-10-18 Updated led footprints to have placement information about orientation.
2013-10-18 Updated aspirin v2.2 to r1
2014-01-30 fix SHT75 humidity board, add 90 degrees version of SHT75 board
2014-04-11 STM32F4 Daughterboard initioal
    Daughterboard for the STM32F4 Discovery, only tht components
2014-04-15 added mouser bom and redme
2014-05-02 fixed align of the main header
    The Main pin header (for the dosvocery board) was offset in the previous
    version.
2015-07-31 added .pro and dxf outline
    Updated with 2015-07-30 6023 on Windows. Added DXF file containing board
    outline + holes. Added KiCAD project file.
2015-09-17 add gps_13 pdf
2016-05-03 SD Logger for Lisa/S
2016-05-04 Added prototype of connector shield Lisa/S with Walkera Genius CPv2
2016-07-05 Updated V2.1 Lisa/M(X) hardware to the final production version.
2016-09-18 Lia breakout board for HITL and testing
2016-09-18 Box for the Lia breakout board
2016-09-18 Lia breakout board (#22)
    * Lia breakout board for HITL and testing
    * Box for the Lia breakout board
2016-09-18 Viking EVCU initial commit
2016-09-18 Viking EVCU initial commit (#23)
2017-02-25 Add 3d-printed damper for Bebop2
2017-03-04 [ecu] Added design files
2017-06-23 fix simple typo
2017-06-23 update typofix
2017-06-24 typo fix (#24)
2017-06-27 decawave arduino
2017-06-27 Lisa-MX-S v1.0
2017-06-27 decawave arduino (#25)
2017-06-27 Lisa-MX-S v1.0 (#26)
